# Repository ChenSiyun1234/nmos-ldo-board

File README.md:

# NMOS LDO

A 1.0 V, 1 A low-dropout regulator built from a power NMOS and an op amp. Four-layer board in KiCad 10, simulated in ngspice.

The target was 1.0 V at 1 A from a 1.5 to 2.0 V input with less than 200 mV of dropout. It ended up at 90 mV at 1 A. Everything here is simulated: ngspice for the circuit, and a small thermal model built from the board's copper.

| Top | Bottom |
|---|---|
|  |  |

## How it works

The awkward part of a 1 V regulator is the gate drive. With a PMOS pass device the gate can only go down to ground, so on a 1.5 V input you only get about 1.5 V of V<sub>GS</sub> and the on-resistance gets ugly. I used an NMOS source follower instead and gave the error amp its own 5 V rail, so the gate can sit up to about 4 V above the source. Q1 is an IRLR024N in DPAK, which has plenty of margin at that drive.

The error amp is an OPA365 running as a PI controller. A source follower is nice to compensate because it only adds one pole, but that pole moves a lot with load: about 30 Hz at no load and 1.4 kHz at 1 A. The crossover moves with it, from about 2 kHz up to 180 kHz. I put the PI zero at 1.25 kHz, just under the light-load crossover, and added a 5 mA preload so the pole can't drift any lower. Light load is where this circuit gets touchy, and the worst case I found over load, capacitor ESR and part tolerances was 56° of phase margin.

The rest is mostly housekeeping:

- The feedback divider reads the output right at the output terminal through two net ties, so the copper between Q1 and the terminal doesn't count. Q1's source moves 2.6 mV from 0 to 1 A, while the terminal moves 0.001 mV.
- A TPS3808 keeps the regulator off until VIN is above about 1.37 V, then waits 20 ms.
- Soft start is just an RC on the 0.8 V set point: 3.7 ms from 10 to 90%, with no overshoot.

## Simulation results

| | Target | Simulated |
|---|---|---|
| Output voltage | 1.000 V ±1% | 1.000 V |
| Dropout at 1 A | < 200 mV | 90 mV |
| Load step, 10 mA to 1 A in 1 µs | ±30 mV | −8.7 / +7.4 mV |
| PSRR at 1 / 10 / 100 kHz | 60 / 40 / 30 dB | 99 / 81 / 63 dB |
| Worst-case phase margin | > 45° | 56° |
| Soft start, 10 to 90% | 1 to 10 ms | 3.7 ms |
| Q1 junction at 1 W, 25 °C | < 125 °C | 58 °C |

Loop gain at 0 A, 10 mA and 1 A. I broke the loop at the sense line and used Middlebrook's double injection, since the impedances on both sides of that node are close.

| | |
|---|---|
|  |  |
| Load step from 10 mA to 1 A at 1 A/µs. The output dips 8.7 mV and is back within 1 mV in about 0.3 ms. | PSRR from VIN. At 1 A the lowest point between 10 Hz and 1 MHz is 50 dB at 355 kHz. |
|  |  |
| Enable at 1 ms and disable at 16 ms, with no load and with a 1 Ω load. With no load the inrush peaks at 0.35 A while the output capacitors charge. | Phase margin against output capacitor ESR. It never drops below 57°, so the loop doesn't depend on ESR. |

## Layout

| Top copper | Bottom copper |
|---|---|
|  |  |

Four layers, 54 × 42 mm, with both inner layers as solid ground. I was aiming for 50 × 40 mm, but the three screw terminals and the M3 holes took more room than I expected.

- The power path is one straight line along the top edge: J1, C1 and C2, Q1, C3 to C6, J2. The control parts stay below it, out of the high-current loop.
- Q1's tab sits on a VIN pour with 30 vias down to a bigger pour on the bottom layer. In the thermal model those vias are worth about 6 °C: 58 °C with them, 64 °C without.
- The reference and the divider return to their own ground island, which only meets the main ground at the output terminal.

## Files

```
hardware/  KiCad project
fab/       Gerbers, drill, BOM, pick and place, STEP
sim/       ngspice models and the Python that runs each analysis
results/   plots, metrics.csv and the raw data behind each plot
scripts/   Python that generates the schematic and board files
docs/      design notes, schematic PDF and images
```

To rerun the simulations you need Python 3 with numpy, scipy, matplotlib and pillow, plus the ngspice shared library (the one that ships with KiCad works):

```
python sim/run_all.py
```

The hand calculations, the remaining plots, the part models and the rebuild steps are in [docs/design-notes.md](docs/design-notes.md).

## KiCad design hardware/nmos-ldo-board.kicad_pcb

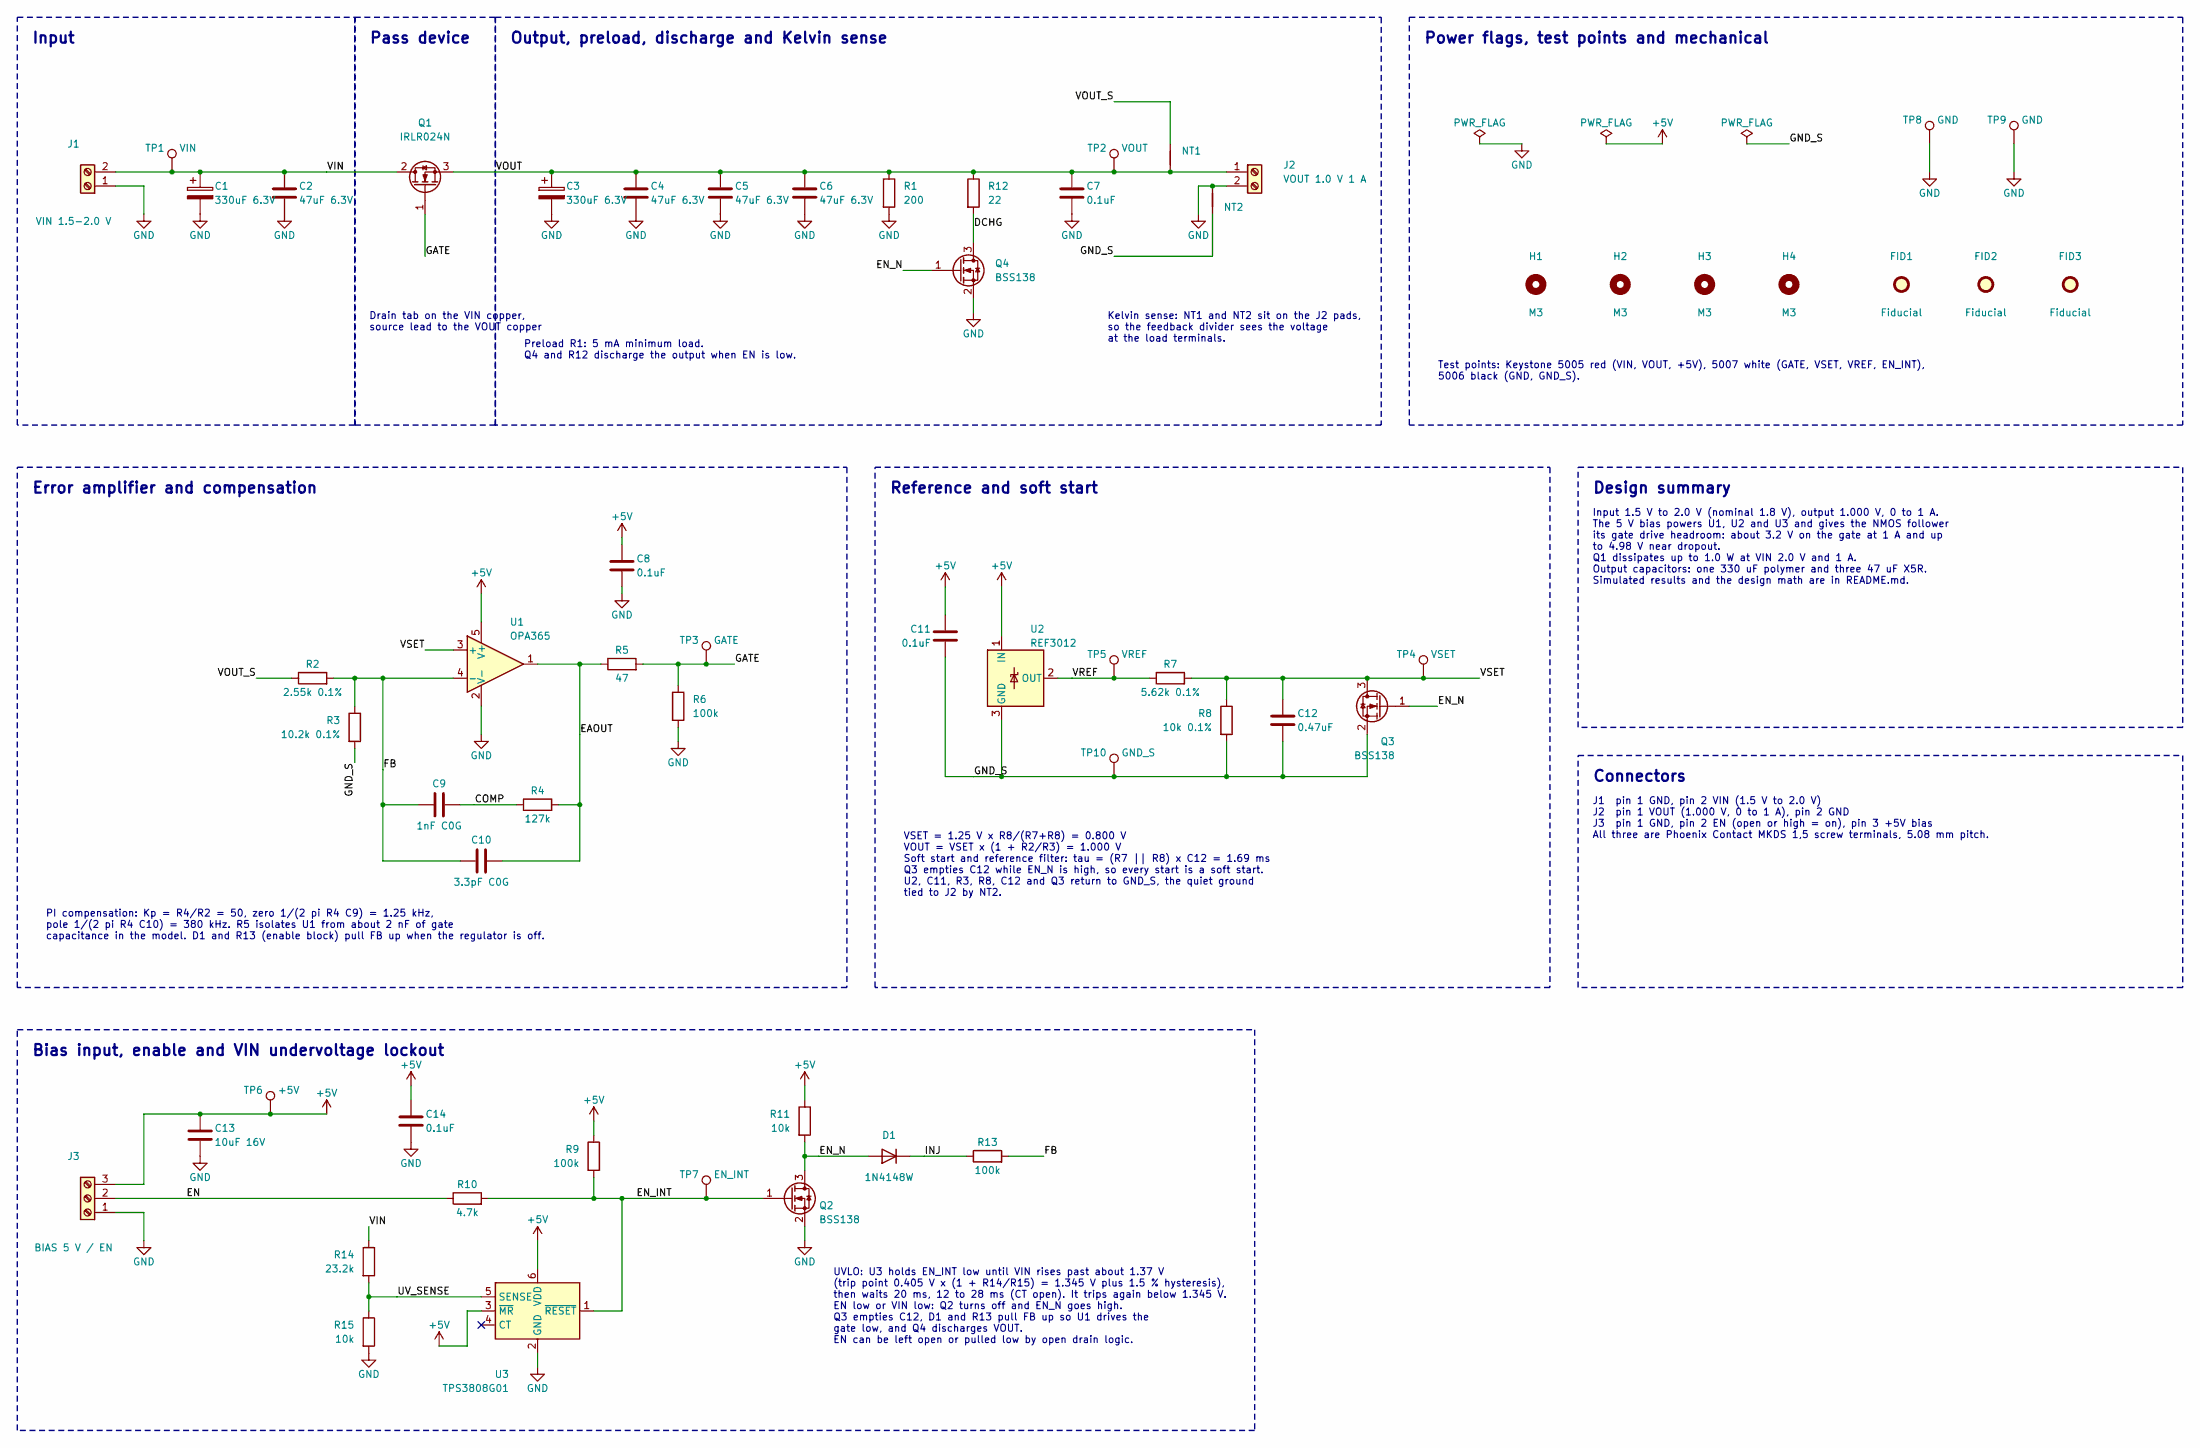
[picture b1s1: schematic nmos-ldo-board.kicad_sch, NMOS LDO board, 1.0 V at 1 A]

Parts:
C1, C3: 330uF 6.3V; CP_EIA-7343-31_Kemet-D; MPN T520D337M006ATE015
C2, C4, C5, C6: 47uF 6.3V; C_1206_3216Metric; MPN GRM31CR60J476ME19L
C7, C8, C11, C14: 0.1uF; C_0603_1608Metric; MPN GRM188R71C104KA01D
C9: 1nF C0G; C_0603_1608Metric; MPN GRM1885C1H102JA01D
C10: 3.3pF C0G; C_0603_1608Metric; MPN GRM1885C1H3R3CA01D
C12: 0.47uF; C_0603_1608Metric; MPN GRM188R71C474KA88D
C13: 10uF 16V; C_0805_2012Metric; MPN GRM21BR61C106KE15L
D1: 1N4148W; D_SOD-123; MPN 1N4148W-7-F
FID1, FID2, FID3: Fiducial; Fiducial_1mm_Mask2mm
H1, H2, H3, H4: M3; MountingHole_3.2mm_M3
J1: VIN 1.5-2.0 V; TerminalBlock_Phoenix_MKDS-1,5-2-5.08_1x02_P5.08mm_Horizont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; MPN 1715721
J2: VOUT 1.0 V 1 A; TerminalBlock_Phoenix_MKDS-1,5-2-5.08_1x02_P5.08mm_Horizont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; MPN 1715721
J3: BIAS 5 V / EN; TerminalBlock_Phoenix_MKDS-1,5-3-5.08_1x03_P5.08mm_Horizont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; MPN 1715734
NT1, NT2: NetTie; NetTie-2_SMD_Pad0.5mm
Q1: IRLR024N; TO-252-2; MPN IRLR024NTRPBF
Q2, Q3, Q4: BSS138; SOT-23; MPN BSS138
R1: 200; R_0603_1608Metric; MPN RC0603FR-07200RL
R2: 2.55k 0.1%; R_0603_1608Metric; MPN RT0603BRD072K55L
R3: 10.2k 0.1%; R_0603_1608Metric; MPN RT0603BRD0710K2L
R4: 127k; R_0603_1608Metric; MPN RC0603FR-07127KL
R5: 47; R_0603_1608Metric; MPN RC0603FR-0747RL
R6, R9, R13: 100k; R_0603_1608Metric; MPN RC0603FR-07100KL
R7: 5.62k 0.1%; R_0603_1608Metric; MPN RT0603BRD075K62L
R8: 10k 0.1%; R_0603_1608Metric; MPN RT0603BRD0710KL
R10: 4.7k; R_0603_1608Metric; MPN RC0603FR-074K7L
R11, R15: 10k; R_0603_1608Metric; MPN RC0603FR-0710KL
R12: 22; R_0603_1608Metric; MPN RC0603FR-0722RL
R14: 23.2k; R_0603_1608Metric; MPN RC0603FR-0723K2L
TP1: VIN; TestPoint_Keystone_5005-5009_Compact; MPN 5005
TP2: VOUT; TestPoint_Keystone_5005-5009_Compact; MPN 5005
TP3: GATE; TestPoint_Keystone_5005-5009_Compact; MPN 5007
TP4: VSET; TestPoint_Keystone_5005-5009_Compact; MPN 5007
TP5: VREF; TestPoint_Keystone_5005-5009_Compact; MPN 5007
TP6: +5V; TestPoint_Keystone_5005-5009_Compact; MPN 5005
TP7: EN_INT; TestPoint_Keystone_5005-5009_Compact; MPN 5007
TP8, TP9: GND; TestPoint_Keystone_5005-5009_Compact; MPN 5006
TP10: GND_S; TestPoint_Keystone_5005-5009_Compact; MPN 5006
U1: OPA365; SOT-23-5; MPN OPA365AIDBVR
U2: REF3012; SOT-23; MPN REF3012AIDBZR
U3: TPS3808G01; SOT-23-6; MPN TPS3808G01DBVR

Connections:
+5V: C8.1, C11.1, C13.1, C14.1, J3.3, R9.1, R11.1, TP6.1, U1.5 (V+), U2.1 (IN), U3.3 (~MR), U3.6 (VDD)
/COMP: C9.2, R4.1
/DCHG: Q4.3 (D), R12.2
/EAOUT: C10.2, R4.2, R5.1, U1.1
/EN: J3.2, R10.1
/EN_INT: Q2.1 (G), R9.2, R10.2, TP7.1, U3.1 (~RESET)
/EN_N: D1.2 (A), Q2.3 (D), Q3.1 (G), Q4.1 (G), R11.2
/FB: C9.1, C10.1, R2.2, R3.1, R13.2, U1.4 (-)
/GATE: Q1.1 (G), R5.2, R6.1, TP3.1
/GND_S: C11.2, C12.2, NT2.2, Q3.2 (S), R3.2, R8.2, TP10.1, U2.3 (GND)
/INJ: D1.1 (K), R13.1
/UV_SENSE: R14.2, R15.1, U3.5 (SENSE)
/VIN: C1.1, C2.1, J1.2, Q1.2 (D), R14.1, TP1.1
/VOUT: C3.1, C4.1, C5.1, C6.1, C7.1, J2.1, NT1.1, Q1.3 (S), R1.1, R12.1, TP2.1
/VOUT_S: NT1.2, R2.1
/VREF: R7.1, TP5.1, U2.2 (OUT)
/VSET: C12.1, Q3.3 (D), R7.2, R8.1, TP4.1, U1.3 (+)
GND: C1.2, C2.2, C3.2, C4.2, C5.2, C6.2, C7.2, C8.2, C13.2, C14.2, J1.1, J2.2, J3.1, NT2.1, Q2.2 (S), Q4.2 (S), R1.2, R6.2, R15.2, TP8.1, TP9.1, U1.2 (V-), U3.2 (GND)

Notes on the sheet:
Input
Pass device
Output, preload, discharge and Kelvin sense
Power flags, test points and mechanical
Error amplifier and compensation
Reference and soft start
Design summary
Connectors
J1 pin 1 GND, pin 2 VIN (1.5 V to 2.0 V) J2 pin 1 VOUT (1.000 V, 0 to 1 A), pin 2 GND J3 pin 1 GND, pin 2 EN (open or high = on), pin 3 +5V bias All three are Phoenix Contact MKDS 1,5 screw terminals, 5.08 mm pitch.
Bias input, enable and VIN undervoltage lockout
Drain tab on the VIN copper, source lead to the VOUT copper
Preload R1: 5 mA minimum load. Q4 and R12 discharge the output when EN is low.
Kelvin sense: NT1 and NT2 sit on the J2 pads, so the feedback divider sees the voltage at the load terminals.
Test points: Keystone 5005 red (VIN, VOUT, +5V), 5007 white (GATE, VSET, VREF, EN_INT), 5006 black (GND, GND_S).
PI compensation: Kp = R4/R2 = 50, zero 1/(2 pi R4 C9) = 1.25 kHz, pole 1/(2 pi R4 C10) = 380 kHz. R5 isolates U1 from about 2 nF of gate capacitance in the model. D1 and R13 (enable block) pull FB up when the regulator is off.
VSET = 1.25 V x R8/(R7+R8) = 0.800 V VOUT = VSET x (1 + R2/R3) = 1.000 V Soft start and reference filter: tau = (R7 || R8) x C12 = 1.69 ms Q3 empties C12 while EN_N is high, so every start is a soft start. U2, C11, R3, R8, C12 and Q3 return to GND_S, the quiet ground tied to J2 by NT2.
Input 1.5 V to 2.0 V (nominal 1.8 V), output 1.000 V, 0 to 1 A. The 5 V bias powers U1, U2 and U3 and gives the NMOS follower its gate drive headroom: about 3.2 V on the gate at 1 A and up to 4.98 V near dropout. Q1 dissipates up to 1.0 W at VIN 2.0 V and 1 A. Output capacitors: one 330 uF polymer 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
UVLO: U3 holds EN_INT low until VIN rises past about 1.37 V (trip point 0.405 V x (1 + R14/R15) = 1.345 V plus 1.5 % hysteresis), then waits 20 ms, 12 to 28 ms (CT open). It trips again below 1.345 V. EN low or VIN low: Q2 turns off and EN_N goes high. Q3 empties C12, D1 and R13 pull FB up so U1 dr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

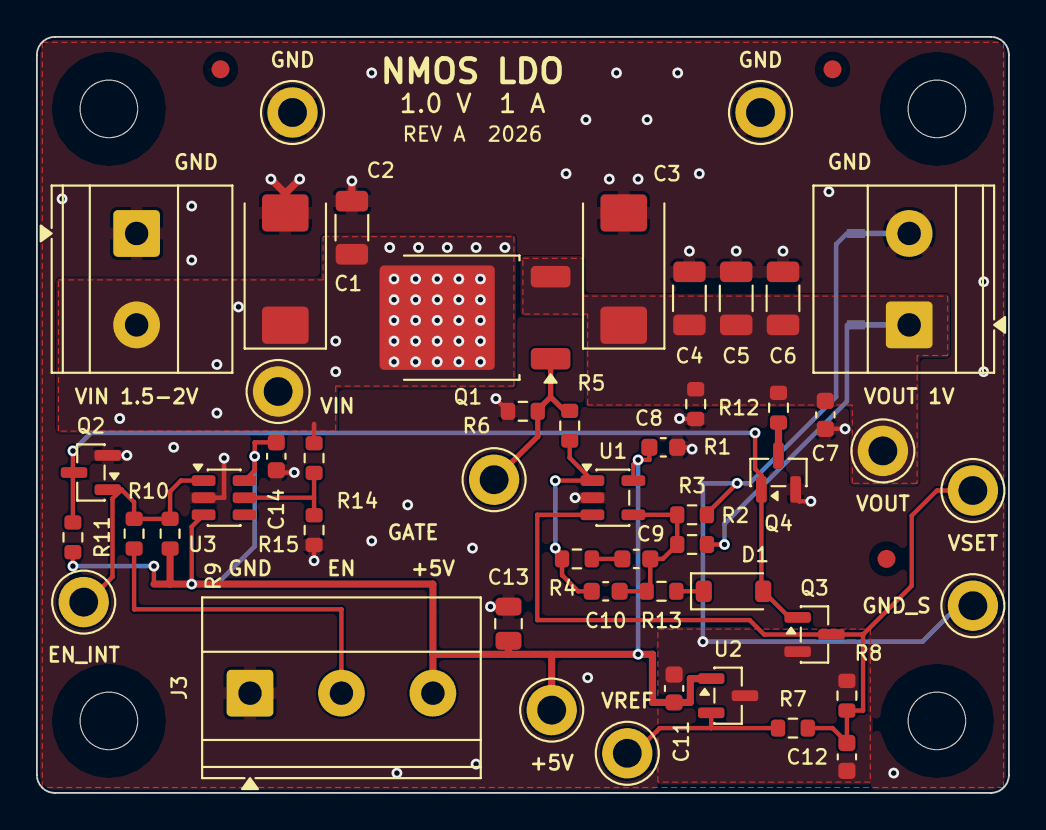
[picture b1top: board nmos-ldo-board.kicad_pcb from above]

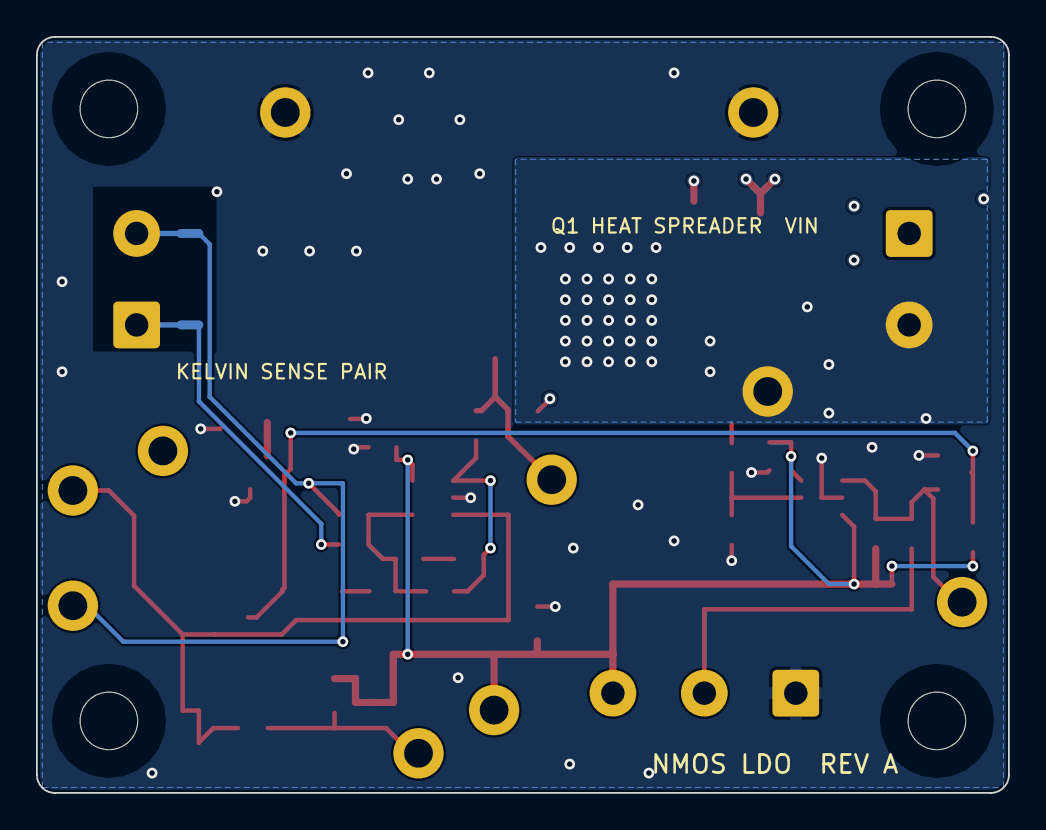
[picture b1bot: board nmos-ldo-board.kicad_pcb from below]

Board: 4 copper layers, 54.0 x 42.0 mm, 59 parts (2 on the bottom side), 18 nets.

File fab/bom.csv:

"Reference","Qty","Value","Description","Manufacturer","MPN","Footprint"
"C1,C3","2","330uF 6.3V","Polymer tantalum capacitor 330uF 6.3V","KEMET","T520D337M006ATE015","Capacitor_Tantalum_SMD:CP_EIA-7343-31_Kemet-D"
"C2,C4,C5,C6","4","47uF 6.3V","Ceramic capacitor 47uF 6.3V","Murata","GRM31CR60J476ME19L","Capacitor_SMD:C_1206_3216Metric"
"C7,C8,C11,C14","4","0.1uF","Ceramic capacitor 0.1uF","Murata","GRM188R71C104KA01D","Capacitor_SMD:C_0603_1608Metric"
"C9","1","1nF C0G","Ceramic capacitor 1nF C0G","Murata","GRM1885C1H102JA01D","Capacitor_SMD:C_0603_1608Metric"
"C10","1","3.3pF C0G","Ceramic capacitor 3.3pF C0G","Murata","GRM1885C1H3R3CA01D","Capacitor_SMD:C_0603_1608Metric"
"C12","1","0.47uF","Ceramic capacitor 0.47uF","Murata","GRM188R71C474KA88D","Capacitor_SMD:C_0603_1608Metric"
"C13","1","10uF 16V","Ceramic capacitor 10uF 16V","Murata","GRM21BR61C106KE15L","Capacitor_SMD:C_0805_2012Metric"
"D1","1","1N4148W","Switching diode, 100 V, 300 mA, SOD-123","Diodes Incorporated","1N4148W-7-F","Diode_SMD:D_SOD-123"
"J1","1","VIN 1.5-2.0 V","Screw terminal, 2 pole, 5.08 mm","Phoenix Contact","1715721","TerminalBlock_Phoenix:TerminalBlock_Phoenix_MKDS-1,5-2-5.08_1x02_P5.08mm_Horizontal"
"J2","1","VOUT 1.0 V 1 A","Screw terminal, 2 pole, 5.08 mm","Phoenix Contact","1715721","TerminalBlock_Phoenix:TerminalBlock_Phoenix_MKDS-1,5-2-5.08_1x02_P5.08mm_Horizontal"
"J3","1","BIAS 5 V / EN","Screw terminal, 3 pole, 5.08 mm","Phoenix Contact","1715734","TerminalBlock_Phoenix:TerminalBlock_Phoenix_MKDS-1,5-3-5.08_1x03_P5.08mm_Horizontal"
"Q1","1","IRLR024N","N-channel logic level MOSFET, 55 V, 65 mohm, DPAK","Infineon","IRLR024NTRPBF","Package_TO_SOT_SMD:TO-252-2"
"Q2,Q3,Q4","3","BSS138","50V Vds, 0.22A Id, N-Channel MOSFET, SOT-23","onsemi","BSS138","Package_TO_SOT_SMD:SOT-23"
"R1","1","200","Resistor 200, 0603","Yageo","RC0603FR-07200RL","Resistor_SMD:R_0603_1608Metric"
"R2","1","2.55k 0.1%","Resistor 2.55k 0.1%, 0603","Yageo","RT0603BRD072K55L","Resistor_SMD:R_0603_1608Metric"
"R3","1","10.2k 0.1%","Resistor 10.2k 0.1%, 0603","Yageo","RT0603BRD0710K2L","Resistor_SMD:R_0603_1608Metric"
"R4","1","127k","Resistor 127k, 0603","Yageo","RC0603FR-07127KL","Resistor_SMD:R_0603_1608Metric"
"R5","1","47","Resistor 47, 0603","Yageo","RC0603FR-0747RL","Resistor_SMD:R_0603_1608Metric"
"R6,R9,R13","3","100k","Resistor 100k, 0603","Yageo","RC0603FR-07100KL","Resistor_SMD:R_0603_1608Metric"
"R7","1","5.62k 0.1%","Resistor 5.62k 0.1%, 0603","Yageo","RT0603BRD075K62L","Resistor_SMD:R_0603_1608Metric"
"R8","1","10k 0.1%","Resistor 10k 0.1%, 0603","Yageo","RT0603BRD0710KL","Resistor_SMD:R_0603_1608Metric"
"R10","1","4.7k","Resistor 4.7k, 0603","Yageo","RC0603FR-074K7L","Resistor_SMD:R_0603_1608Metric"
"R11,R15","2","10k","Resistor 10k, 0603","Yageo","RC0603FR-0710KL","Resistor_SMD:R_0603_1608Metric"
"R12","1","22","Resistor 22, 0603","Yageo","RC0603FR-0722RL","Resistor_SMD:R_0603_1608Metric"
"R14","1","23.2k","Resistor 23.2k, 0603","Yageo","RC0603FR-0723K2L","Resistor_SMD:R_0603_1608Metric"
"TP1","1","VIN","Test point, red","Keystone Electronics","5005","TestPoint:TestPoint_Keystone_5005-5009_Compact"
"TP2","1","VOUT","Test point, red","Keystone Electronics","5005","TestPoint:TestPoint_Keystone_5005-5009_Compact"
"TP3","1","GATE","Test point, white","Keystone Electronics","5007","TestPoint:TestPoint_Keystone_5005-5009_Compact"
"TP4","1","VSET","Test point, white","Keystone Electronics","5007","TestPoint:TestPoint_Keystone_5005-5009_Compact"
"TP5","1","VREF","Test point, white","Keystone Electronics","5007","TestPoint:TestPoint_Keystone_5005-5009_Compact"
"TP6","1","+5V","Test point, red","Keystone Electronics","5005","TestPoint:TestPoint_Keystone_5005-5009_Compact"
"TP7","1","EN_INT","Test point, white","Keystone Electronics","5007","TestPoint:TestPoint_Keystone_5005-5009_Compact"
"TP8,TP9","2","GND","Test point, black","Keystone Electronics","5006","TestPoint:TestPoint_Keystone_5005-5009_Compact"
"TP10","1","GND_S","Test point, black","Keystone Electronics","5006","TestPoint:TestPoint_Keystone_5005-5009_Compact"
"U1","1","OPA365","50-MHz, Zero-Crossover, Low-Distortion, High CMRR, RRI/O, Single-Supply, SOT-23-5","Texas Instruments","OPA365AIDBVR","Package_TO_SOT_SMD:SOT-23-5"
"U2","1","REF3012","1.25 V voltage reference, 0.2 % initial accuracy, SOT-23-3","Texas Instruments","REF3012AIDBZR","Package_TO_SOT_SMD:SOT-23"
"U3","1","TPS3808G01","Low-Quiescent-Current, Programmable-Delay Supervisory Circuit, SOT-23-6","Texas Instruments","TPS3808G01DBVR","Package_TO_SOT_SMD:SOT-23-6"

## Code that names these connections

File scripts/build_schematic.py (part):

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section("Design summary", 297.18, 104.14, 406.4, 151.13)
section("Connectors", 297.18, 156.21, 406.4, 198.12)
text("J1  pin 1 GND, pin 2 VIN (1.5 V to 2.0 V)" + chr(10) +
     "J2  pin 1 VOUT (1.000 V, 0 to 1 A), pin 2 GND" + chr(10) +
     "J3  pin 1 GND, pin 2 EN (open or high = on), pin 3 +5V bias" + chr(10) +
     "All three are Phoenix Contact MKDS 1,5 screw terminals, 5.08 mm pitch.", 299.72, 163.83)
section("Bias input, enable and VIN undervoltage lockout", 15.24, 205.74, 238.76, 278.13)
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          nets={"1": "GATE", "2": "VIN", "3": "VOUT"}, ref_at=(88.9, 41.91, ""), val_at=(88.9, 44.45, ""),
          desc="N-channel logic level MOSFET, 55 V, 65 mohm, DPAK")
W(q["1"], (88.9, 66.04))
label("GATE", 88.9, 66.04)
text("Drain tab on the VIN copper,\nsource lead to the VOUT copper", 78.74, 76.2)

# ---- output
W(q["3"], (233.68, 50.8))
label("VOUT", 101.6, 50.8)
cap("C3", 111.76, 54.61, "330uF 6.3V", FP_POLY, "T520D337M006ATE015", {"1": "VOUT", "2": "GND"}, polar=True)
power("GND", 111.76, 58.42)
for ref, x in (("C4", 127.0), ("C5", 142.24), ("C6", 157.48)):
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           nets={"1": "EN_N", "2": "GND", "3": "DCHG"}, ref_at=(191.77, 67.31, "left"),
           val_at=(191.77, 69.85, "left"))
W(r["2"], qd["3"])
label("DCHG", 187.96, 60.96)
W(qd["2"], (187.96, 76.2))
power("GND", 187.96, 76.2)
W(qd["1"], (175.26, 68.58))
label("EN_N", 175.26, 68.58, 180)
text("Preload R1: 5 mA minimum load.\nQ4 and R12 discharge the output when EN is low.", 106.68, 81.28)
cap("C7", 205.74, 54.61, "0.1uF", FP_C0603, "GRM188R71C104KA01D", {"1": "VOUT", "2": "GND"})
power("GND", 205.74, 58.42)
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            ref_at=(227.33, 46.99, ""), val_at=(227.33, 46.99, ""), fields_vis=False,
            in_bom=False, desc="Net tie, Kelvin sense of VOUT at J2")
W(nt1["2"], (223.52, 38.1), (213.36, 38.1))
label("VOUT_S", 213.36, 38.1, 180)
W(j2["2"], (228.6, 53.34), (228.6, 58.42))
power("GND", 228.6, 58.42)
nt2 = place("NT2", "Device", "NetTie_2", 231.14, 55.88, rot=270, value="NetTie",
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W(u1["2"], (99.06, 152.4))
power("GND", 99.06, 152.4)
W(u1["3"], (88.9, 137.16))
label("VSET", 88.9, 137.16, 180)
W(u1["4"], (81.28, 142.24))
r2 = res("R2", 68.58, 142.24, "2.55k 0.1%", "RT0603BRD072K55L", {"1": "VOUT_S", "2": "FB"}, rot=90,
         ref_at=(68.58, 139.7, ""), val_at=(68.58, 144.78, ""))
W(r2["2"], (81.28, 142.24))
W(r2["1"], (58.42, 142.24))
label("VOUT_S", 58.42, 142.24, 180)
r3 = res("R3", 76.2, 151.13, "10.2k 0.1%", "RT0603BRD0710K2L", {"1": "FB", "2": "GND_S"},
         ref_at=(73.66, 149.86, "right"), val_at=(73.66, 152.4, "right"))
W(r3["1"], (76.2, 142.24))
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label("GND_S", 76.2, 157.48, 270)
W((81.28, 142.24), (81.28, 175.26))
label("FB", 81.28, 158.75, 0)
c9 = cap("C9", 91.44, 165.1, "1nF C0G", FP_C0603, "GRM1885C1H102JA01D", {"1": "FB", "2": "COMP"}, rot=90,
         ref_at=(91.44, 161.29, ""), val_at=(91.44, 168.91, ""))
W((81.28, 165.1), c9["1"])
r4 = res("R4", 109.22, 165.1, "127k", "RC0603FR-07127KL", {"1": "COMP", "2": "EAOUT"}, rot=90,
         ref_at=(109.22, 162.56, ""), val_at=(109.22, 167.64, ""))
W(c9["2"], r4["1"])
label("COMP", 97.79, 165.1)
W(r4["2"], (116.84, 165.1))
c10 = cap("C10", 99.06, 175.26, "3.3pF C0G", FP_C0603, "GRM1885C1H3R3CA01D", {"1": "FB", "2": "EAOUT"},
          rot=90, ref_at=(99.06, 171.45, ""), val_at=(99.06, 179.07, ""))
W((81.28, 175.26), c10["1"])
W(c10["2"], (116.84, 175.26))
W(u1["1"], (116.84, 139.7), (116.84, 175.26))
label("EAOUT", 116.84, 152.4)
r5 = res("R5", 124.46, 139.7, "47", "RC0603FR-0747RL", {"1": "EAOUT", "2": "GATE"}, rot=90,
         ref_at=(124.46, 137.16, ""), val_at=(124.46, 142.24, ""))
W((116.84, 139.7), r5["1"])
W(r5["2"], (144.78, 139.7))
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W(r6["2"], (134.62, 153.67))
power("GND", 134.62, 153.67)
tp("TP3", 139.7, 139.7, "GATE", "white", "5007")
label("GATE", 144.78, 139.7)
c8 = cap("C8", 124.46, 121.92, "0.1uF", FP_C0603, "GRM188R71C104KA01D", {"1": "+5V", "2": "GND"})
W(c8["1"], (124.46, 116.84))
power("+5V", 124.46, 116.84)
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W(u2["2"], (219.71, 142.24))
label("VREF", 205.74, 142.24)
tp("TP5", 213.36, 142.24, "VREF", "white", "5007")
r7 = res("R7", 223.52, 142.24, "5.62k 0.1%", "RT0603BRD075K62L", {"1": "VREF", "2": "VSET"}, rot=90,
         ref_at=(223.52, 139.7, ""), val_at=(223.52, 144.78, ""))
W(r7["2"], (279.4, 142.24))
r8 = res("R8", 233.68, 149.86, "10k 0.1%", "RT0603BRD0710KL", {"1": "VSET", "2": "GND_S"},
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           val_at=(264.16, 156.21, "left"))
W(q3["2"], (259.08, 160.02))
W(q3["1"], (271.78, 147.32))
label("EN_N", 271.78, 147.32)
tp("TP4", 269.24, 142.24, "VSET", "white", "5007")
label("VSET", 279.4, 142.24)
tp("TP10", 213.36, 160.02, "GND_S", "black", "5006")
text("VSET = 1.25 V x R8/(R7+R8) = 0.800 V\n"
     "VOUT = VSET x (1 + R2/R3) = 1.000 V\n"
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tp("TP6", 60.96, 220.98, "+5V", "red", "5005")
W(j3["1"], (38.1, 238.76), (38.1, 243.84))
power("GND", 38.1, 243.84)
r10 = res("R10", 96.52, 236.22, "4.7k", "RC0603FR-074K7L", {"1": "EN", "2": "EN_INT"}, rot=90,
          ref_at=(96.52, 233.68, ""), val_at=(96.52, 238.76, ""))
W(j3["2"], r10["1"])
label("EN", 45.72, 236.22)
W(r10["2"], (149.86, 236.22))
label("EN_INT", 127.0, 236.22)
r9 = res("R9", 119.38, 228.6, "100k", "RC0603FR-07100KL", {"1": "+5V", "2": "EN_INT"},
         ref_at=(116.84, 227.33, "right"), val_at=(116.84, 229.87, "right"))
W(r9["1"], (119.38, 222.25))
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power("+5V", 91.44, 262.89)
noconnect(*u3["4"])
W(u3["5"], (78.74, 254.0))
label("UV_SENSE", 83.82, 254.0)
r14 = res("R14", 78.74, 247.65, "23.2k", "RC0603FR-0723K2L", {"1": "VIN", "2": "UV_SENSE"},
          ref_at=(76.2, 246.38, "right"), val_at=(76.2, 248.92, "right"))
W(r14["1"], (78.74, 241.3))
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power("+5V", 157.48, 215.9)
W(r11["2"], q2["3"])
W((157.48, 228.6), (168.91, 228.6))
label("EN_N", 160.02, 228.6)
d1 = place("D1", "Diode", "1N4148W", 172.72, 228.6, rot=180, value="1N4148W",
           footprint="Diode_SMD:D_SOD-123", mpn="1N4148W-7-F", mfr="Diodes Incorporated",
           nets={"1": "INJ", "2": "EN_N"}, ref_at=(172.72, 224.79, ""), val_at=(172.72, 232.41, ""),
           desc="Switching diode, 100 V, 300 mA, SOD-123")
r13 = res("R13", 190.5, 228.6, "100k", "RC0603FR-07100KL", {"1": "INJ", "2": "FB"}, rot=90,
          ref_at=(190.5, 226.06, ""), val_at=(190.5, 231.14, ""))
W(d1["1"], r13["1"])
label("INJ", 179.07, 228.6)
W(r13["2"], (200.66, 228.6))
label("FB", 200.66, 228.6)
text("UVLO: U3 holds EN_INT low until VIN rises past about 1.37 V\n"
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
